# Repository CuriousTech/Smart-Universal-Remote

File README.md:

# Smart-Universal-Remote  
Smart Universal Remote using one of these:  
[Waveshare ESP32-S3-Touch-LCD-1.28](https://www.waveshare.com/wiki/ESP32-S3-Touch-LCD-1.28)  
[Waveshare ESP32-S3-Touch-LCD-1.69](https://www.waveshare.com/wiki/ESP32-S3-Touch-LCD-1.69)  
[WaveShare-ESP32-S3-Touch-LCD-2.8](https://www.waveshare.com/wiki/ESP32-S3-Touch-LCD-2.8)  
[WaveShare-ESP32-S3-Touch-LCD-2inch](https://www.waveshare.com/wiki/ESP32-S3-Touch-LCD-2)  

This is a tiny smart universal remote with WiFi, IR, capacitive touchscreen, wireless charging (and possibly Bluetooth) all for a very low cost.  
  
Parts list:  
  
[AliExpress ESP32-S3-Touch-1.28](https://www.aliexpress.us/item/3256806026101753.html?spm=a2g0o.order_list.order_list_main.5.eb321802K7vxRh&gatewayAdapt=glo2usa) This includes the 12p connector with dupont ends.  
  
[AliExpress ESP32-S3-Touch-1.69](https://www.aliexpress.us/item/3256806781994387.html?spm=a2g0o.order_list.order_list_main.5.6e661802Im2eg3&gatewayAdapt=glo2usa)  Or this one. It seems they've fixed the original issue, but I'm not buying another one to test it. [Subreddit thread](https://www.reddit.com/r/esp32/comments/1cxmo5r/esp32s3_169inch_touch_display_features_6axis_imu/)  
  
[AliExpress ESP32-S3-Touch-2.8](https://www.aliexpress.us/item/3256807168316377.html?spm=a2g0o.order_list.order_list_main.11.654e1802WfmOyY&gatewayAdapt=glo2usa) My new favorite. Comes with dupont connectors, speakers (not yet implemented). No M2.5 screws, but not hard to find. The wireless charging pad may need to go on the back of the case due to screws.  
  
[eBay:Charger pad](https://www.ebay.com/itm/143351559508?var=442544081497) Select USB-C. These can be bought anywhere.  For the latest model, the charger can be centered. The edges of the pad can be bent because the wrapper is a bit oversized. A USB-C cable or magnetic connector will work as well.  

[eBay:battery](https://www.ebay.com/itm/174781170731?var=473957762104) Select 1.25mm plug. This is probably a decent size. Be careful with the polarity. It was correct on mine. They sell a 1500mAh that's just a little thicker, but I may add a keypad that will use the extra space.   

[TinkerCAD Case Models](https://www.tinkercad.com/things/j1XckJlfVuT-waveshare-esp32-s3-touch-128-remote-case) For editing the 3D print models.  
  
[New IRIO board on OSHPark](https://oshpark.com/shared_projects/KRJOFbjO)  I used some double-sided tape to make sure it doesn't touch the other board.  
  
This IR sender/receiver is designed to be built easily using common parts, but Arduino IR modules should be compatible.  If using an NPN transistor for the sender, subtract the vF from 3.3 for R1 plus the IR LED vF. 110 ohms should be good for a MOSFET and 1.2V LED.  
  
The web page. This is used to decode remotes and test output commands. Just hit the decode button and start pushing buttons on a remote. Those values can be entered in the button code[4] array of any buttons created. Mixed remotes on one page, or all the same. Doesn't matter.

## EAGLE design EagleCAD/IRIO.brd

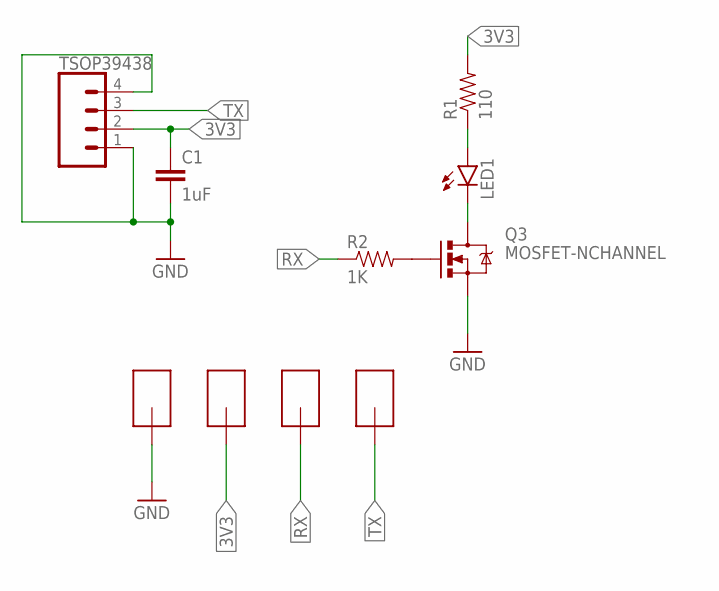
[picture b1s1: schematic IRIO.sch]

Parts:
C1: 1uF; 0805
LED1: LED5MM
Q3: MOSFET-NCHANNEL; SOT23-3
R1: 110; 0805
R2: 1K; 0805
TSOP39438: CONN_041.27MM; 1X04_1.27MM
U$1, U$2, U$3, U$4: SMD-PAD1SMD-PAD80X32; SMD-PAD6

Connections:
3V3: C1.1, R1.2, TSOP39438.2, U$3.>PAD
GND: C1.2, Q3.2 (S), TSOP39438.1, TSOP39438.4, U$2.>PAD
unnamed: LED1.A, R1.1
unnamed: Q3.1 (G), R2.2
unnamed: LED1.K (C), Q3.3 (D)
RX: R2.1, U$1.>PAD
TX: TSOP39438.3, U$4.>PAD

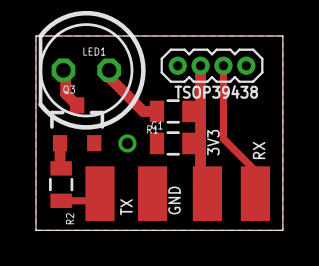
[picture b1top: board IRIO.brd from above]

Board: 2 copper layers, 13.7 x 10.8 mm, 10 parts (0 on the bottom side), 7 nets.

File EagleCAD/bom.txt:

RC  TSOP394388
R1  110 ohm 0805
R2  1K 0805
C1  1uF 0805
Q3  N-channel SOT-23 (ex. SSM3K333RLF)
LED1 3mm IR LED (had some laying around)

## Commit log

2024-02-28 Delete URemote/watchFace.h
    Not used to save lots of space
2024-02-29 Abandoning the ESP32C3-MINI version
2024-02-29 Added a dimension to the screens
2024-02-29 Auto format 2 dim screens based on screen row value
2024-02-29 Abandoning the ESP32C3 model
2024-03-06 Gave up on battery monitor
2024-03-08 1mm taller for better IRIO fitment
2024-03-11 Added a warning about damage
2024-03-11 Changed screen to tile
2024-03-28 Delete 3D/URButton.stl
    New model, no button
2024-03-28 Waveshare model case
2024-03-28 Changed IR pins for new model
2024-03-28 Updated for the Waveshare display board
2024-03-28 Added charging detect
2024-03-30 Copy to TFT_eSPI/User_Setups and include in Usere_Setup_Select.h
2024-04-01 A bit tighter
2024-04-01 Added light sleep mostly
2024-04-01 Mostly light sleep code added
2024-04-01 Added sleep and timezone settings
2024-04-02 A little safety for sleep
2024-04-02 Replaced a screensaver
2024-04-02 Changed text flag
2024-04-02 Added garage door opener, changed text flag, faster swipe speed
2024-04-04 Example script for PC connection
2024-04-04 Accelerometer testing moslty
2024-04-04 Dimmer slider updater
2024-04-04 Cleanup, added another screensaver
2024-04-05 Reverted to last
2024-04-05 Removed calls to draw inside callback (unstable)
2024-04-09 Added battery meter
2024-04-09 Added more data in PC interface
2024-04-09 Changed a flag name
2024-04-09 More arc, horiz, vert sliders
2024-04-09 Work on sliders, QMI just used for motion
2024-04-09 Example script for media connection
2024-05-05 added host IP
2024-05-05 Switched to WebSocket client
2024-05-05 Added brightness slider
2024-05-05 Brightness slider, volt avg
2024-05-05 Not useable
2024-05-05 Newer design
2024-05-22 Slimmer design with TSOP39438
2024-05-22 Updated ESPAsyncWebserver
2024-05-22 Rewrote swipe UI
2024-05-22 Rewrote swipe UI and H/V slider
2024-05-22 Switched from EEPROM to fat file
2024-05-22 Added snap-back on swipe
2024-05-23 Corrected footprint for TSOP39438
2024-05-27 Same as included Setup302_Waveshare_ESP32S3_GC9A01.h
2024-05-27 Use for 240x280 1.69"
2024-05-27 external pin defs
2024-05-27 Resolution set externally
2024-05-27 Less fixed res stuff
2024-05-27 Additions for a 240x280 display
2024-05-28 Changed config info at top for 1.69" module
2024-05-30 Not used
2024-05-30 Removed problematic 1.69" features
2024-05-30 Removed problematic 1.69" code
2024-06-20 Non-round battery meter
2024-06-20 Single sprite swipe, non-round display compatible
2024-06-30 Removed button.ID
2024-07-23 Updated IRIO link
2024-07-23 global bg color
2024-07-23 Added unused text functions
2024-07-23 Removed test code
2025-01-04 Flipped for easy USB access
2025-01-04 added ROTATE_DISPLAY for new flipped case
2025-01-14 Case for WaveShare ESP32S3 2.8
2025-01-14 For WS 2.8"
2025-01-14 Added WS 2.8"
2025-01-14 Added batt max value calibration
2025-01-14 TFT_eSPI Setup file for WaveShare-ESP32-Touch-2.8
2025-01-14 Added 2.8"
2025-01-21 Replaced arrow images with drawn
2025-01-21 Wrong arrows from testing
2025-01-21 Forgot a signed value needed
2025-01-26 Alignment padding
2025-01-26 A few issues found with the 2.8"
2025-01-30 Add files via upload
    Betterer
2025-01-30 TP_INT for 2.8" fix, added rect for buttons
2025-01-30 Added rect for buttons, cleaner
2025-01-30 Removed unneeded light IP
2025-02-27 Added web file up/dnload/del
2025-02-27 Added slider text
2025-02-27 Drag/drop file upload, dload, delete button
2025-03-01 Single part case for 2.8"
2025-03-10 increased some things to 16 bit
2025-03-10 Added a file manager page
2025-03-10 FileList array
2025-03-10 Changed from file to prefs
2025-03-10 File manager mods, smaller WebSocket client
2025-03-10 Added SD card sup for 2.8"
2025-03-10 Added SD card support
2025-03-10 16 bit light levels
2025-03-10 Forgot to define ROUND_DISPLAY
2025-03-10 Added power off button
2025-03-11 Forgot to add active arc slider labels
2025-04-17 For Waveshare 2inch
2025-04-17 touch pos was 8 bit
2025-04-17 Pin setup for 2"
2025-04-17 SD card for 2" (SPI)
2025-04-17 Pin setup for 2" SPI SD
2025-04-20 Added 2" link
2025-04-22 Multi-file drag and drop
2025-09-14 using esp32 time lib
2025-09-14 battery % stuff

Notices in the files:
parts and their libraries:
SparkFun-Passives: Licensing: CC v3.0 Share-Alike You are welcome to use this library for commercial purposes.
SparkFun-DiscreteSemi: Licensing: Creative Commons ShareAlike 4.0 International - https://creativecommons.org/licenses/by-sa/4.0
